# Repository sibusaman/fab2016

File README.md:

# Sibu's Fab Academy Documentation
Fab Academy 2016 Documentation License details

All of the documentations unless specified within the file or directory, is licensed under [CC-BY-SA 4.0](https://creativecommons.org/licenses/by-sa/4.0/legalcode) except for the source codes, which are licensed under [GPLv3](https://www.gnu.org/licenses/quick-guide-gplv3.en.html).

The following logo and it's varients are not shared under any licenses.

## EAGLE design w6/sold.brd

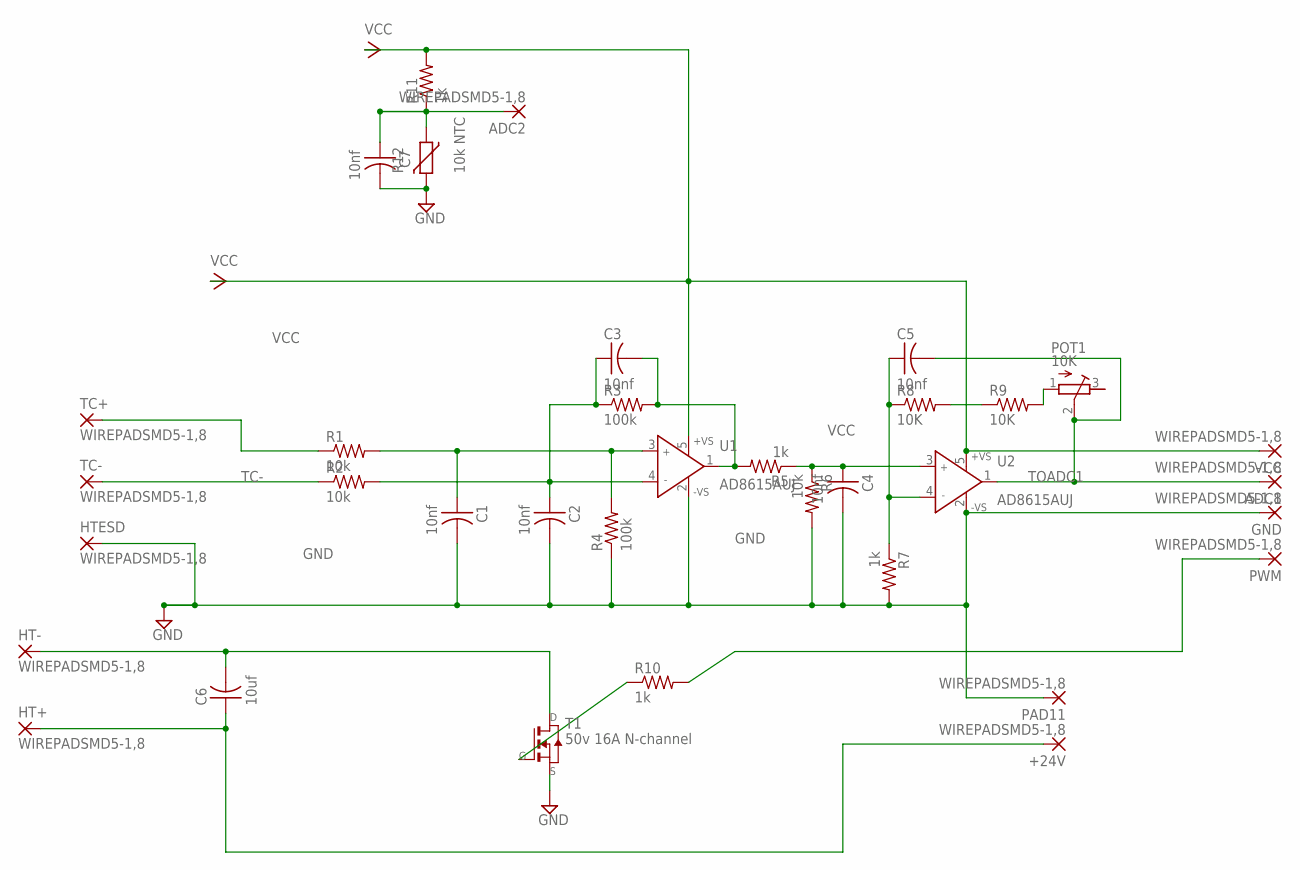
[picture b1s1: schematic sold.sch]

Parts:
+24V: WIREPADSMD5-1,8; 5-1,8
ADC1, ADC2: WIREPADSMD5-1,8; 5-1,8
C1, C2, C3, C4, C5, C7: 10nf; C1206FAB
C6: 10uf; C1206FAB
GND: WIREPADSMD5-1,8; 5-1,8
HT+: WIREPADSMD5-1,8; 5-1,8
HT-: WIREPADSMD5-1,8; 5-1,8
HTESD: WIREPADSMD5-1,8; 5-1,8
PAD11: WIREPADSMD5-1,8; 5-1,8
POT1: 10K; RTRIM3103
PWM: WIREPADSMD5-1,8; 5-1,8
R1, R2, R6: 10k; R1206FAB
R3, R4: 100k; R1206FAB
R5, R7, R10, R11: 1k; R1206FAB
R8, R9: 10K; R1206FAB
R12: 10k NTC; CT/CN1206
T1: 50v 16A N-channel; TO252
TC+: WIREPADSMD5-1,8; 5-1,8
TC-: WIREPADSMD5-1,8; 5-1,8
U1, U2: AD8615AUJ; TSOT23-5
VCC: WIREPADSMD5-1,8; 5-1,8

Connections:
GND: C1.2, C2.2, C4.2, C7.2, GND.1, HTESD.1, PAD11.1, R4.1, R6.2, R7.2, R12.2, T1.2 (S), U1.2 (-VS), U2.2 (-VS)
unnamed: C4.1, R5.1, R6.1, U2.3 (IN+)
unnamed: C2.1, C3.1, R2.2, R3.1, U1.4 (IN-)
unnamed: C3.2, R3.2, R5.2, U1.1 (OUT)
unnamed: R1.1, TC+.1
unnamed: ADC2.1, C7.1, R11.1, R12.1
unnamed: C1.1, R1.2, R4.2, U1.3 (IN+)
unnamed: R8.2, R9.1
unnamed: POT1.1 (A), R9.2
unnamed: C5.1, R7.1, R8.1, U2.4 (IN-)
unnamed: R10.1, T1.1 (G)
unnamed: PWM.1, R10.2
unnamed: +24V.1, C6.1, HT+.1
unnamed: C6.2, HT-.1, T1.3 (D)
TC-: R2.1, TC-.1
TOADC1: ADC1.1, C5.2, POT1.2 (S), U2.1 (OUT)
VCC: R11.2, U1.5 (+VS), U2.5 (+VS), VCC.1

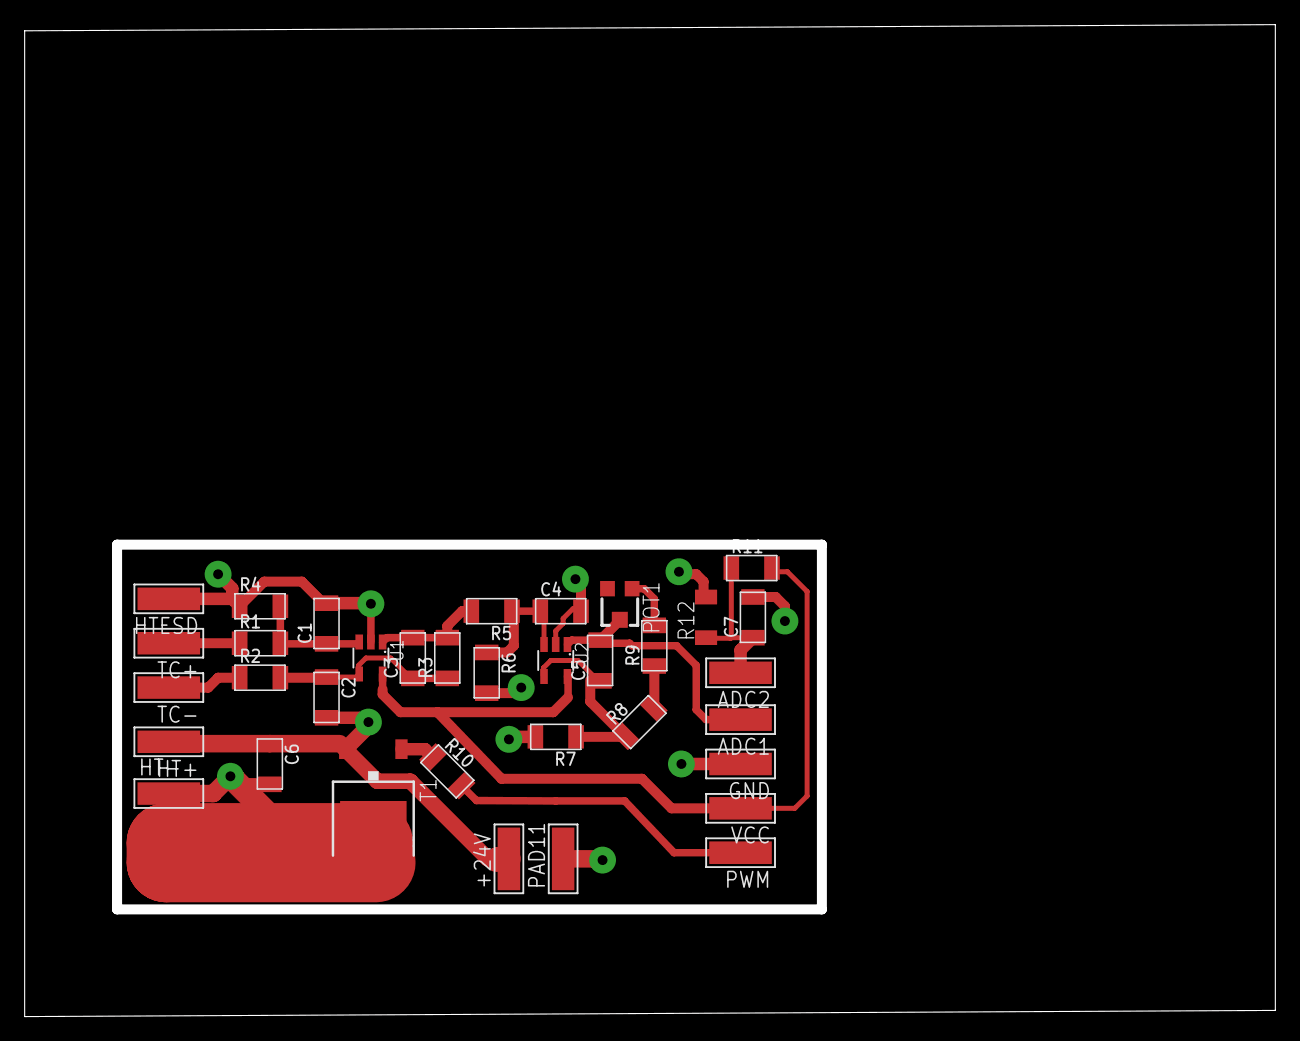
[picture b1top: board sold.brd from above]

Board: 2 copper layers, 101.5 x 80.5 mm, 35 parts (0 on the bottom side), 17 nets.

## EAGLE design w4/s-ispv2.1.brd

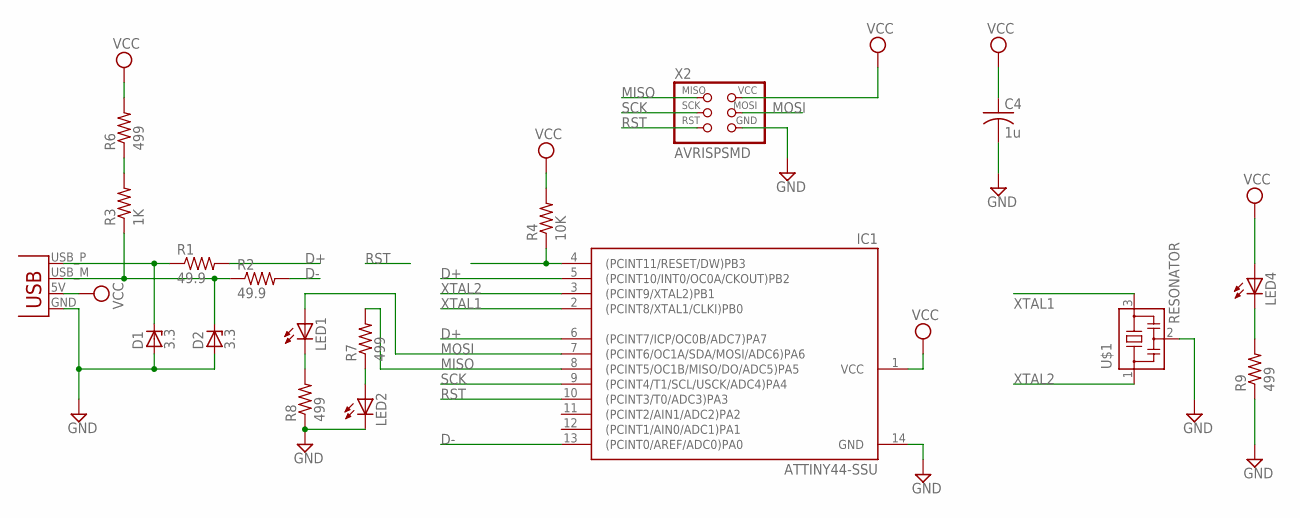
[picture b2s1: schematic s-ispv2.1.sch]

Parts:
C4: 1u; C1206
D1, D2: 3.3; SOD123
IC1: ATTINY44-SSU; SOIC14
LED1, LED2, LED4: LEDSMT1206; 1206
R1, R2: 49.9; R1206
R3: 1K; R1206
R4: 10K; R1206
R6, R7, R8, R9: 499; R1206
U$1: RESONATOR; EFOBM
X1: USBPCB; USB-A-PCB
X2: AVRISPSMD; 2X03SMD

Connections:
D+: IC1.5 ((PCINT10/INT0/OC0A/CKOUT)PB2), IC1.6 ((PCINT7/ICP/OC0B/ADC7)PA7), R1.2
D-: IC1.13 ((PCINT0/AREF/ADC0)PA0), R2.2
GND: C4.2, D1.ANODE, D2.ANODE, IC1.14 (GND), LED2.C, R8.1, R9.1, U$1.2, X1.GND, X2.6 (GND)
MISO: IC1.8 ((PCINT5/OC1B/MISO/DO/ADC5)PA5), R7.2, X2.1 (MISO)
MOSI: IC1.7 ((PCINT6/OC1A/SDA/MOSI/ADC6)PA6), LED1.A, X2.4 (MOSI)
unnamed: D1.CATHODE, R1.1, X1.USB_P (D+)
unnamed: D2.CATHODE, R2.1, R3.1, X1.USB_M (D-)
unnamed: R3.2, R6.1
unnamed: LED1.C, R8.2
unnamed: LED2.A, R7.1
unnamed: LED4.C, R9.2
RST: IC1.4 ((PCINT11/RESET/DW)PB3), IC1.10 ((PCINT3/T0/ADC3)PA3), R4.1, X2.5 (RST)
SCK: IC1.9 ((PCINT4/T1/SCL/USCK/ADC4)PA4), X2.3 (SCK)
VCC: C4.1, IC1.1 (VCC), LED4.A, R4.2, R6.2, X1.5V (VBUS), X2.2 (VCC)
XTAL1: IC1.2 ((PCINT8/XTAL1/CLKI)PB0), U$1.3
XTAL2: IC1.3 ((PCINT9/XTAL2)PB1), U$1.1

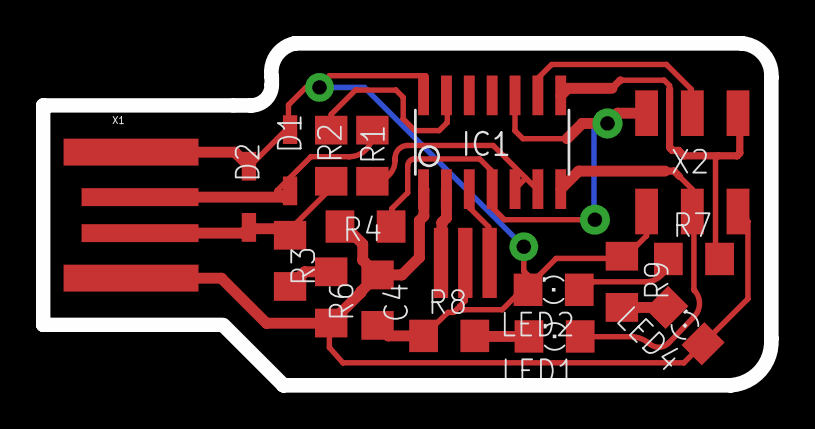
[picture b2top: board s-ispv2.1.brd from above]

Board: 2 copper layers, 40.4 x 19.0 mm, 18 parts (0 on the bottom side), 16 nets.

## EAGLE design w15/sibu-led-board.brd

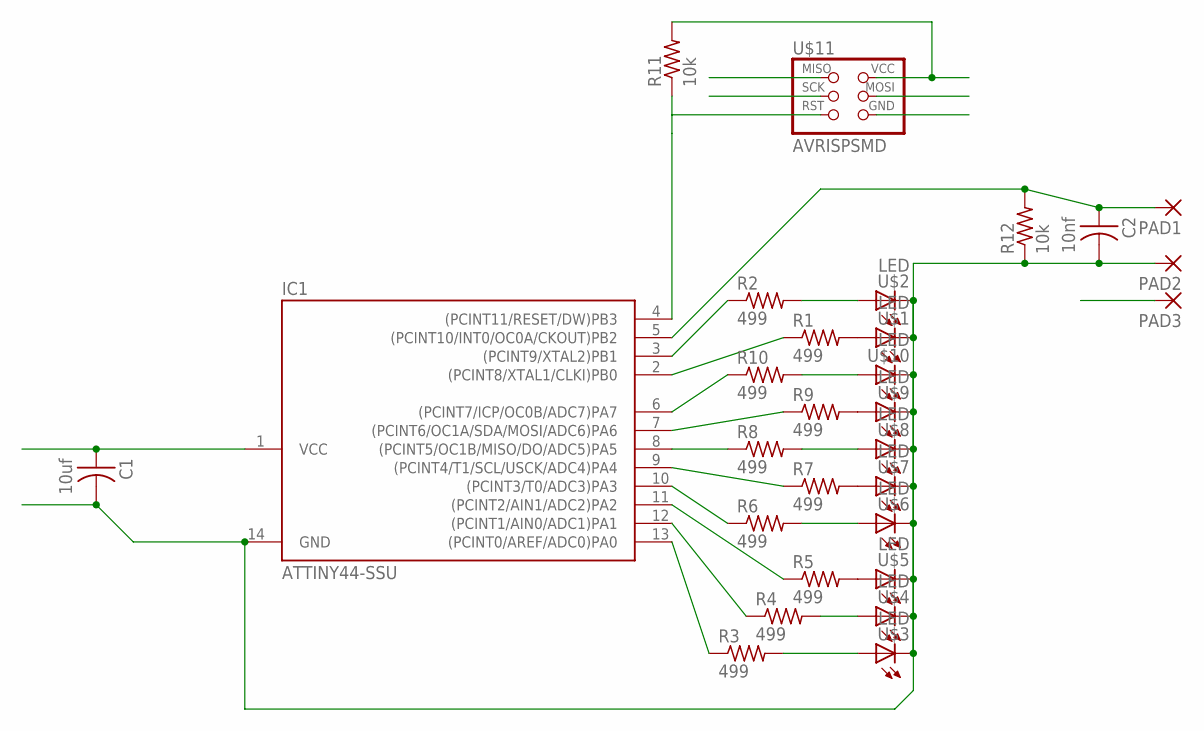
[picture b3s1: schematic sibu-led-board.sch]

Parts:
C1: 10uf; C1206FAB
C2: 10nf; C1206FAB
IC1: ATTINY44-SSU; SOIC14
PAD1, PAD2, PAD3: SMD2; SMD1,27-2,54
R1, R2, R3, R4, R5, R6, R7, R8, R9, R10: 499; R1206FAB
R11, R12: 10k; R1206FAB
U$1, U$2, U$3, U$4, U$5, U$6, U$7, U$8, U$9, U$10: LED; LED1206FAB
U$11: AVRISPSMD; 2X03SMD

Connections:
A0: R3.2, U$3.1 (A)
A1: R4.2, U$4.1 (A)
A2: R5.2, U$5.1 (A)
A3: R6.2, U$6.1 (A)
A4: R7.2, U$7.1 (A)
A5: R8.2, U$8.1 (A)
A6: R9.2, U$9.1 (A)
A7: R10.2, U$10.1 (A)
B0: R1.2, U$1.1 (A)
B1: R2.2, U$2.1 (A)
DATA_IN: C2.1, IC1.5 ((PCINT10/INT0/OC0A/CKOUT)PB2), PAD1.1, R12.2
GND: C1.2, C2.2, IC1.14 (GND), PAD2.1, R12.1, U$1.2 (C), U$2.2 (C), U$3.2 (C), U$4.2 (C), U$5.2 (C), U$6.2 (C), U$7.2 (C), U$8.2 (C), U$9.2 (C), U$10.2 (C), U$11.6 (GND)
MISO: IC1.8 ((PCINT5/OC1B/MISO/DO/ADC5)PA5), R8.1, U$11.1 (MISO)
MOSI: IC1.7 ((PCINT6/OC1A/SDA/MOSI/ADC6)PA6), R9.1, U$11.4 (MOSI)
unnamed: IC1.13 ((PCINT0/AREF/ADC0)PA0), R3.1
unnamed: IC1.12 ((PCINT1/AIN0/ADC1)PA1), R4.1
unnamed: IC1.11 ((PCINT2/AIN1/ADC2)PA2), R5.1
unnamed: IC1.10 ((PCINT3/T0/ADC3)PA3), R6.1
unnamed: IC1.2 ((PCINT8/XTAL1/CLKI)PB0), R1.1
unnamed: IC1.3 ((PCINT9/XTAL2)PB1), R2.1
unnamed: IC1.6 ((PCINT7/ICP/OC0B/ADC7)PA7), R10.1
RST: IC1.4 ((PCINT11/RESET/DW)PB3), R11.1, U$11.5 (RST)
SCK: IC1.9 ((PCINT4/T1/SCL/USCK/ADC4)PA4), R7.1, U$11.3 (SCK)
VCC: C1.1, IC1.1 (VCC), PAD3.1, R11.2, U$11.2 (VCC)

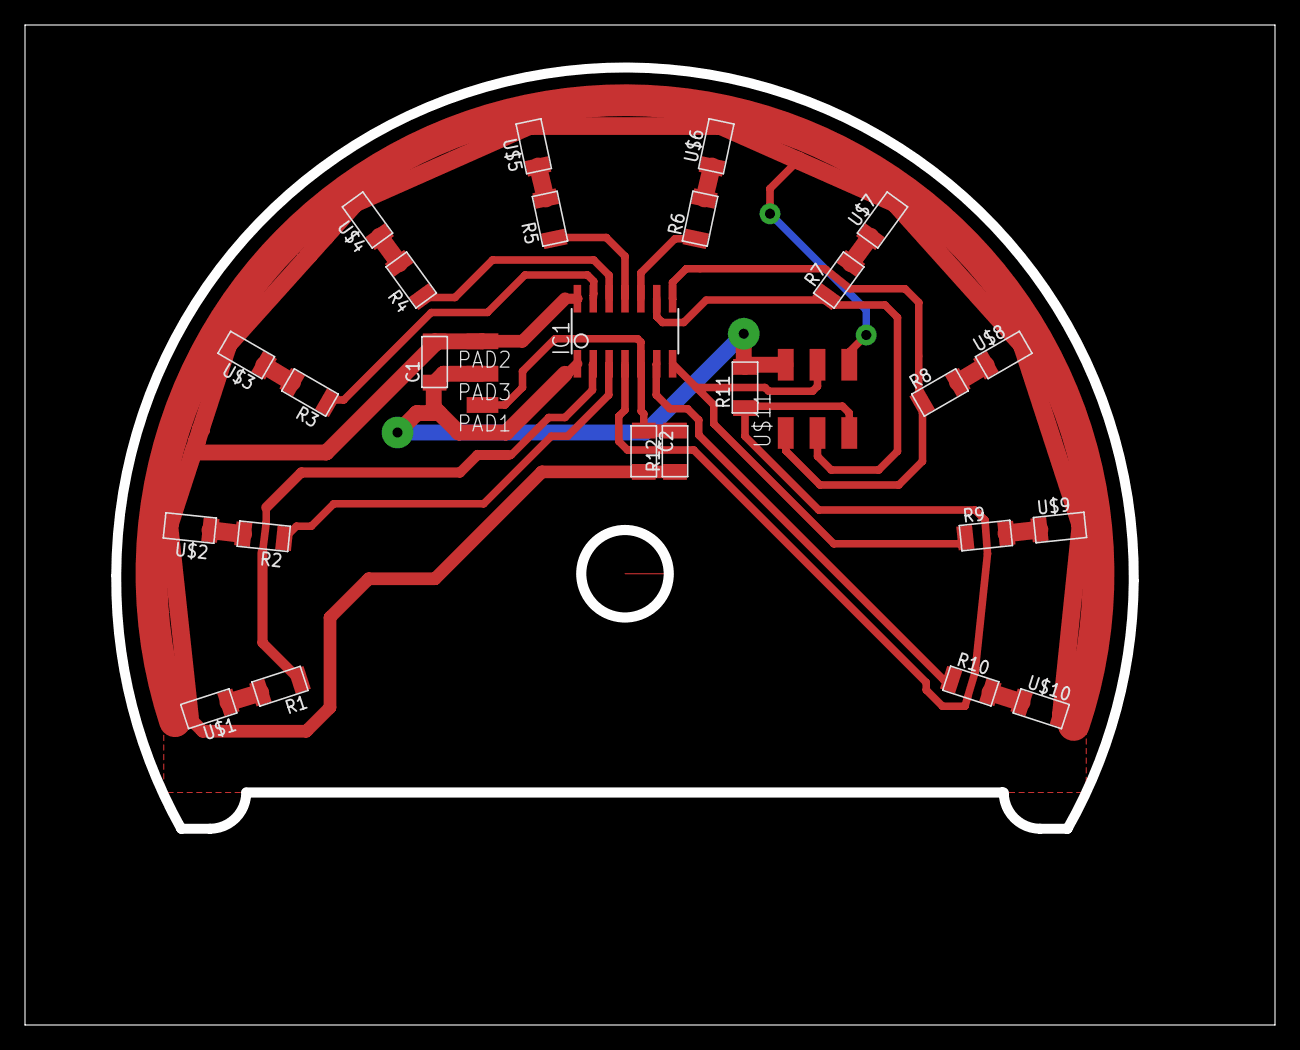
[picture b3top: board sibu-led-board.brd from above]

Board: 2 copper layers, 100.0 x 80.0 mm, 29 parts (0 on the bottom side), 24 nets.

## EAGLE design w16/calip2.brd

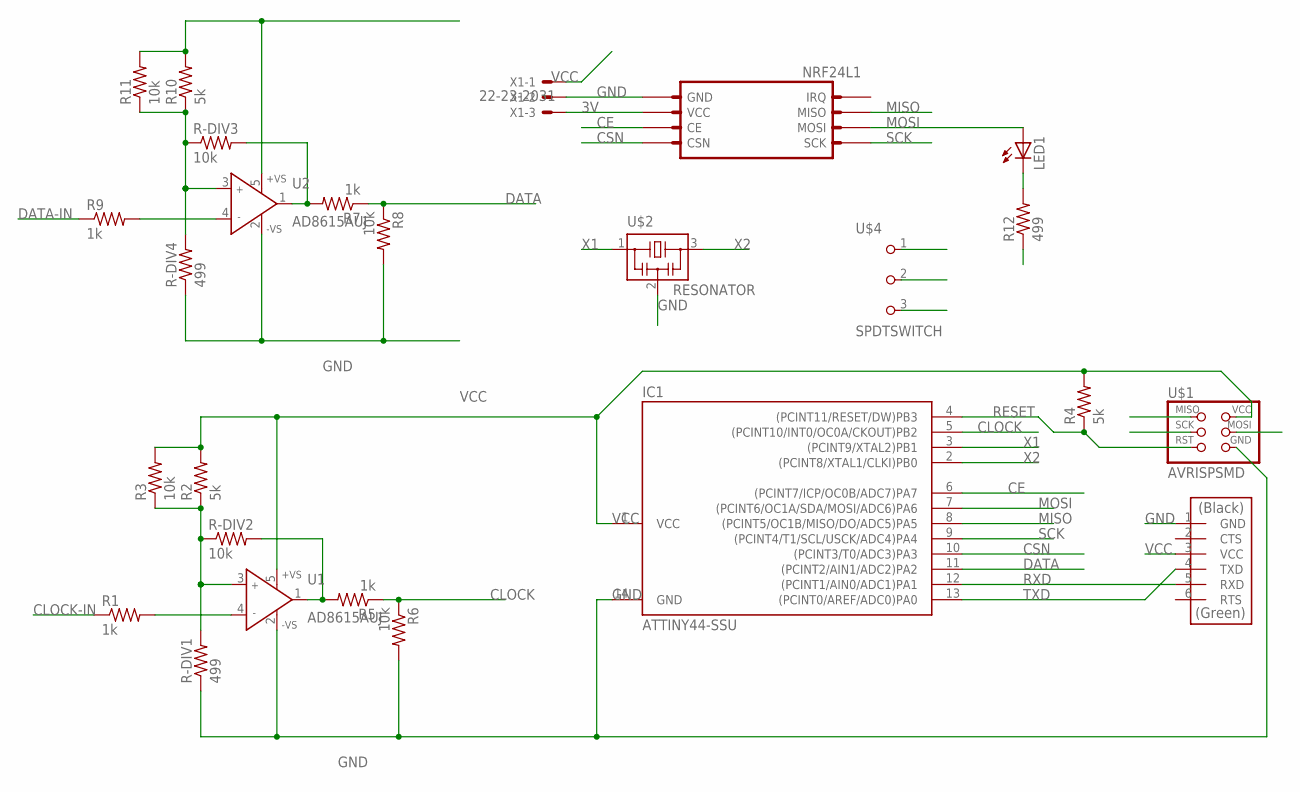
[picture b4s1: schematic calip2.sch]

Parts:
IC1: ATTINY44-SSU; SOIC14
LED1: LEDSML1206; SML1206
NRF24L1: NRF
R1, R5, R7, R9: 1k; R1206FAB
R2, R4, R10: 5k; R1206FAB
R3, R6, R8, R11: 10k; R1206FAB
R12: 499; R1206FAB
R-DIV1, R-DIV4: 499; R1206FAB
R-DIV2, R-DIV3: 10k; R1206FAB
U1, U2: AD8615AUJ; TSOT23-5
U$1: AVRISPSMD; 2X03SMD
U$2: RESONATOR; EFOBM
U$3: FTDI-SMD-HEADER; 1X06SMD
U$4: SPDTSWITCH
X1: 22-23-2031

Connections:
3V: NRF24L1.2 (VCC), X1.3
CE: IC1.6 ((PCINT7/ICP/OC0B/ADC7)PA7), NRF24L1.3 (CE)
CLOCK: IC1.5 ((PCINT10/INT0/OC0A/CKOUT)PB2), R5.1, R6.1
CLOCK-IN: R1.1, U$4.2
CSN: IC1.10 ((PCINT3/T0/ADC3)PA3), NRF24L1.4 (CSN)
DATA: IC1.11 ((PCINT2/AIN1/ADC2)PA2), R7.1, R8.1
DATA-IN: R9.1, U$4.3
GND: IC1.14 (GND), NRF24L1.P$1 (GND), R6.2, R8.2, R12.1, R-DIV1.1, R-DIV4.1, U1.2 (-VS), U2.2 (-VS), U$1.6 (GND), U$2.2, U$3.1 (GND), U$4.1, X1.2
MISO: IC1.8 ((PCINT5/OC1B/MISO/DO/ADC5)PA5), NRF24L1.7 (MISO), U$1.1 (MISO)
MOSI: IC1.7 ((PCINT6/OC1A/SDA/MOSI/ADC6)PA6), LED1.A, NRF24L1.6 (MOSI), U$1.4 (MOSI)
unnamed: R1.2, U1.4 (IN-)
unnamed: LED1.C, R12.2
unnamed: R2.1, R3.1, R-DIV1.2, R-DIV2.1, U1.3 (IN+)
unnamed: R5.2, R-DIV2.2, U1.1 (OUT)
unnamed: R7.2, R-DIV3.2, U2.1 (OUT)
unnamed: R10.1, R11.1, R-DIV3.1, R-DIV4.2, U2.3 (IN+)
unnamed: R9.2, U2.4 (IN-)
RESET: IC1.4 ((PCINT11/RESET/DW)PB3), R4.1, U$1.5 (RST)
RXD: IC1.12 ((PCINT1/AIN0/ADC1)PA1), U$3.5 (RXD)
SCK: IC1.9 ((PCINT4/T1/SCL/USCK/ADC4)PA4), NRF24L1.5 (SCK), U$1.3 (SCK)
TXD: IC1.13 ((PCINT0/AREF/ADC0)PA0), U$3.4 (TXD)
VCC: IC1.1 (VCC), R2.2, R3.2, R4.2, R10.2, R11.2, U1.5 (+VS), U2.5 (+VS), U$1.2 (VCC), U$3.3 (VCC), X1.1
X1: IC1.3 ((PCINT9/XTAL2)PB1), U$2.1
X2: IC1.2 ((PCINT8/XTAL1/CLKI)PB0), U$2.3

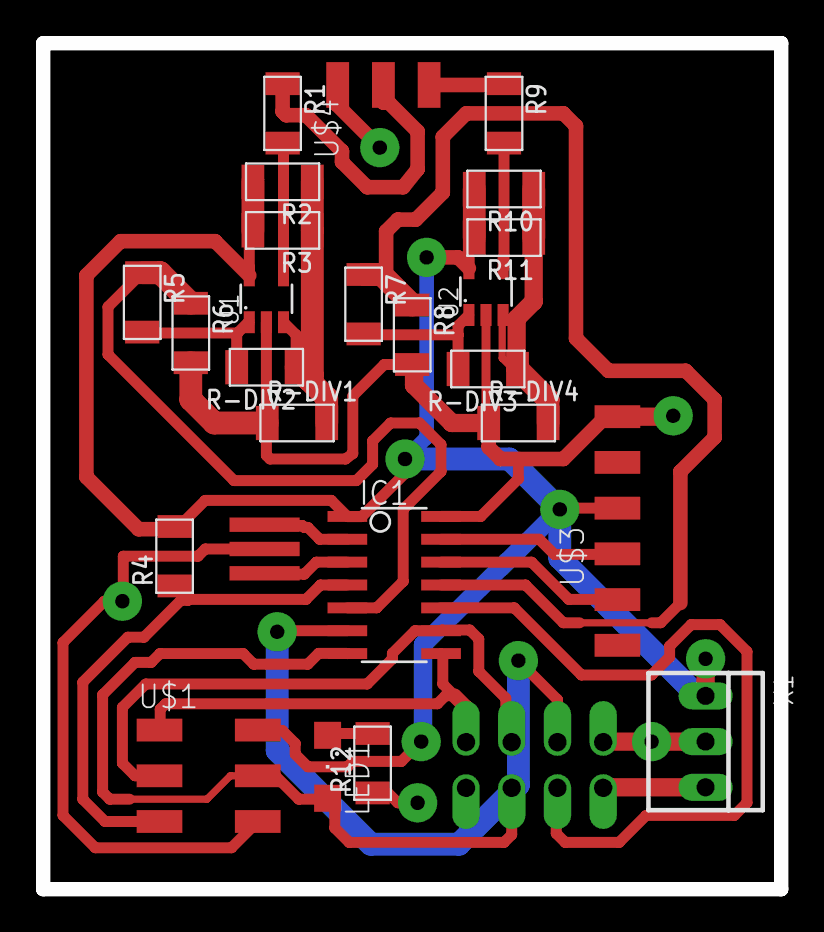
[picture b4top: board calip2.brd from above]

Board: 2 copper layers, 41.0 x 47.0 mm, 26 parts (1 on the bottom side), 24 nets.

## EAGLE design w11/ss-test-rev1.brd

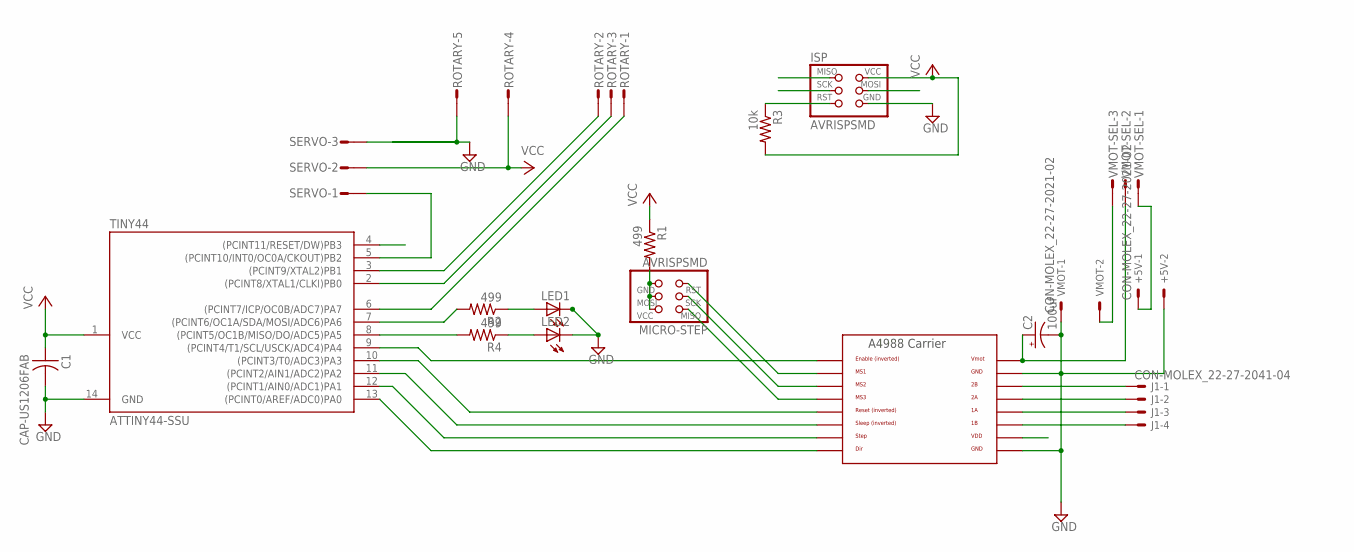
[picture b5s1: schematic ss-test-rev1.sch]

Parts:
+5V: CON-MOLEX_22-27-2021-02; CON-MOLEX_6410-02
A4988: REPRAPJR_A4988BREAKOUT
C1: CAP-US1206FAB; C1206FAB
C2: 100uf; RCL_140CLH-0810
ISP: AVRISPSMD; 2X03SMD
J1: CON-MOLEX_22-27-2041-04; CON-MOLEX_6410-04
LED1, LED2: LED_LEDSML1206; LED_SML1206
MICRO-STEP: AVRISPSMD; 2X03SMD
R1, R2, R4: 499; R1206FAB
R3: 10k; R1206FAB
ROTARY: S05P
SERVO: S03P
TINY44: ATTINY44-SSU; SOIC14
VMOT: CON-MOLEX_22-27-2021-02; CON-MOLEX_6410-02
VMOT-SEL: S03P

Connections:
GND: +5V.2, A4988.GND, A4988.GND@0 (GND), C1.2, C2.-, ISP.6 (GND), LED1.C, LED2.C, ROTARY.5, SERVO.3, TINY44.14 (GND), VMOT.1
MISO: ISP.1 (MISO), R4.2, TINY44.8 ((PCINT5/OC1B/MISO/DO/ADC5)PA5)
MOSI: ISP.4 (MOSI), R2.2, TINY44.7 ((PCINT6/OC1A/SDA/MOSI/ADC6)PA6)
unnamed: A4988.2B, J1.1
unnamed: A4988.2A, J1.2
unnamed: A4988.1A, J1.3
unnamed: A4988.1B, J1.4
unnamed: A4988.MS1, MICRO-STEP.5 (RST)
unnamed: A4988.MS2, MICRO-STEP.3 (SCK)
unnamed: A4988.MS3, MICRO-STEP.1 (MISO)
unnamed: ROTARY.2, TINY44.3 ((PCINT9/XTAL2)PB1)
unnamed: ROTARY.3, TINY44.2 ((PCINT8/XTAL1/CLKI)PB0)
unnamed: A4988.DIR, TINY44.13 ((PCINT0/AREF/ADC0)PA0)
unnamed: A4988.STEP, TINY44.12 ((PCINT1/AIN0/ADC1)PA1)
unnamed: A4988.SLP (SLEEP), TINY44.11 ((PCINT2/AIN1/ADC2)PA2)
unnamed: A4988.RST, TINY44.10 ((PCINT3/T0/ADC3)PA3)
unnamed: LED2.A, R4.1
unnamed: A4988.VMOT, C2.+, VMOT-SEL.2
unnamed: SERVO.1, TINY44.5 ((PCINT10/INT0/OC0A/CKOUT)PB2)
unnamed: MICRO-STEP.2 (VCC), MICRO-STEP.4 (MOSI), MICRO-STEP.6 (GND), R1.2
unnamed: VMOT.2, VMOT-SEL.3
unnamed: ROTARY.1, TINY44.6 ((PCINT7/ICP/OC0B/ADC7)PA7)
unnamed: LED1.A, R2.1
RST: ISP.5 (RST), R3.1, TINY44.4 ((PCINT11/RESET/DW)PB3)
SCK: A4988.EN, ISP.3 (SCK), TINY44.9 ((PCINT4/T1/SCL/USCK/ADC4)PA4)
VCC: +5V.1, A4988.VDD, C1.1, ISP.2 (VCC), R1.1, R3.2, ROTARY.4, SERVO.2, TINY44.1 (VCC), VMOT-SEL.1

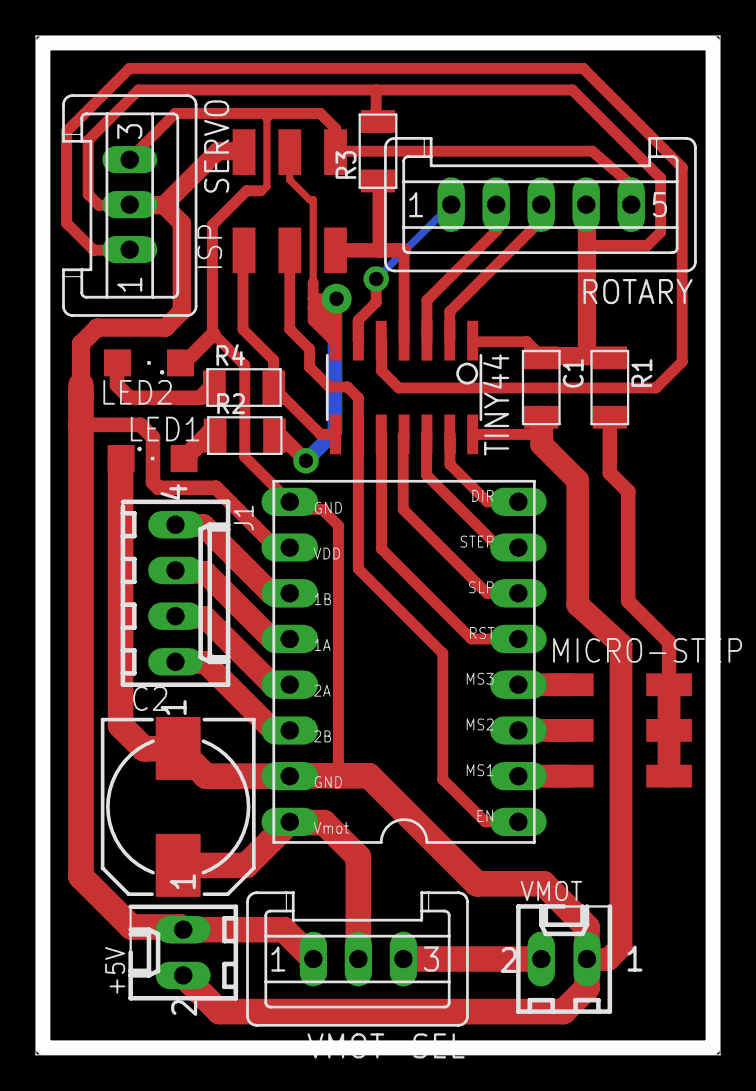
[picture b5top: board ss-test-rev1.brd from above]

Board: 2 copper layers, 38.0 x 56.6 mm, 18 parts (0 on the bottom side), 26 nets.

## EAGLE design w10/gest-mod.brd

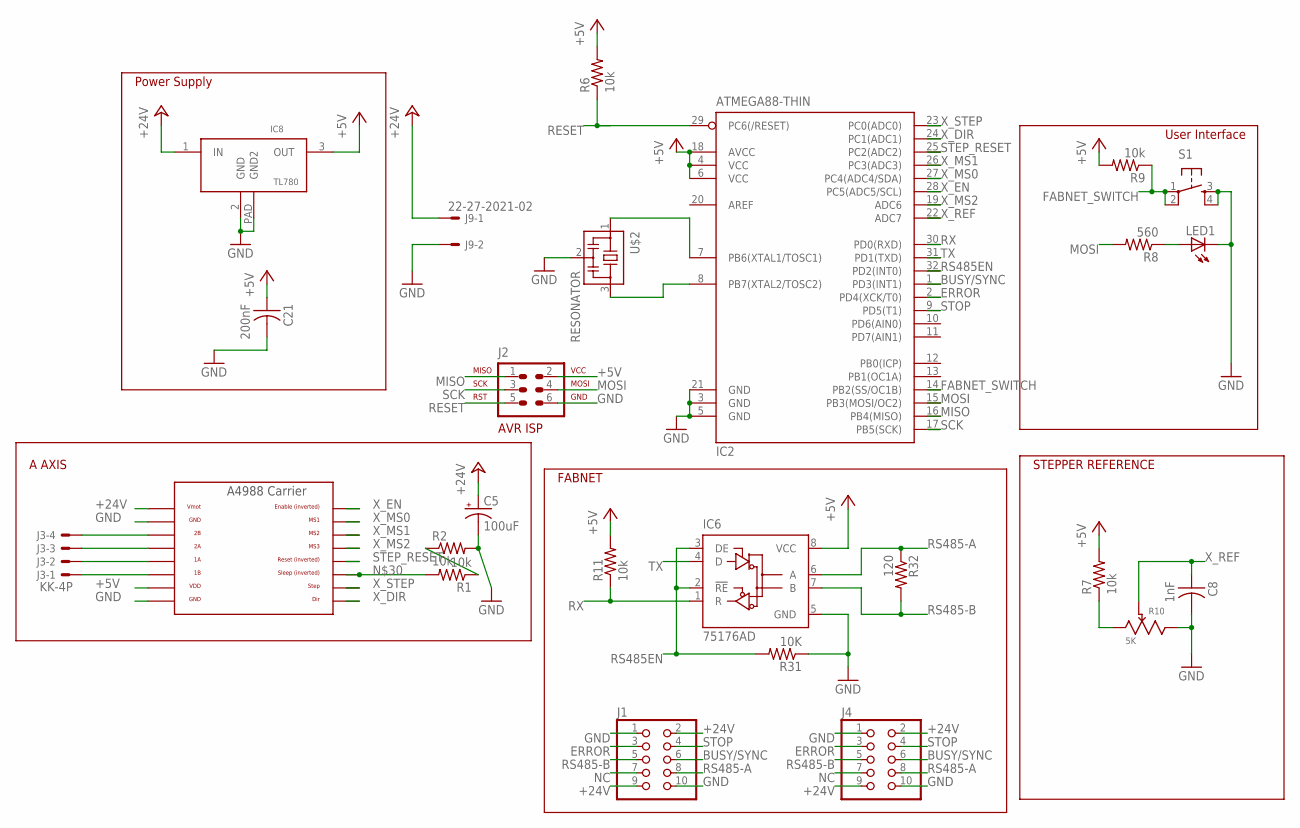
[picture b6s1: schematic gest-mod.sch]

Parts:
C5: 100uF; PANASONIC_D
C8: 1nF; C1206FAB
C21: 200nF; C1206FAB
IC2: ATMEGA88-THIN; TQFP32-08THIN
IC6: 75176AD; D_R-PDSO-G8
IC8: TL780_VREG; D2PAK-3
J1, J4: PINHEAD_PINHD-2X5; PINHEAD_2X05
J2: AVR-7_AVR-ISP-6VERT; AVR-7_AVR-ISP-6
J3: KK-4P; 7395-04
J9: 22-27-2021-02; 6410-02
LED1: LEDCHIPLED_1206; CHIPLED_1206
R1, R2, R6, R7, R9, R11: 10k; R1206FAB
R8: 560; R1206FAB
R10: 5K; BOURN_TRIM
R31: 10K; R1206FAB
R32: 120; R1206FAB
S1: 6MM_SWITCH6MM_SWITCH; 6MM_SWITCH
U$2: RESONATOR; EFOBM
U$5: REPRAPJR_A4988BREAKOUT

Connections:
+5V: C21.1, IC2.4 (VCC), IC2.6 (VCC), IC2.18 (AVCC), IC6.8 (VCC), IC8.3 (OUT), J2.2, R6.2, R7.2, R9.2, R11.2, U$5.VDD
+24V: C5.+, IC8.1 (IN), J1.2, J1.9, J4.2, J4.9, J9.1, U$5.VMOT
BUSY/SYNC: IC2.1 (PD3(INT1)), J1.6, J4.6
ERROR: IC2.2 (PD4(XCK/T0)), J1.3, J4.3
FABNET_SWITCH: IC2.14 (PB2(SS/OC1B)), R9.1, S1.1, S1.2 (P1)
GND: C5.-, C8.2, C21.2, IC2.3 (GND), IC2.5 (GND), IC2.21 (GND), IC6.5 (GND), IC8.2 (GND), IC8.PAD (GND2), J1.1, J1.10, J2.6, J4.1, J4.10, J9.2, LED1.C, R2.2, R10.3, R31.1, S1.3 (S), S1.4 (S1), U$2.2, U$5.GND, U$5.GND@0 (GND)
MISO: IC2.16 (PB4(MISO)), J2.1
MOSI: IC2.15 (PB3(MOSI/OC2)), J2.4, R8.2
N2354: R7.1, R10.1
unnamed: IC2.7 (PB6(XTAL1/TOSC1)), U$2.1
unnamed: IC2.8 (PB7(XTAL2/TOSC2)), U$2.3
unnamed: J3.3, U$5.2A
unnamed: J3.4, U$5.2B
unnamed: LED1.A, R8.1
unnamed: R1.1, R2.1
unnamed: J3.2, U$5.1A
unnamed: J3.1, U$5.1B
unnamed: R1.2, U$5.SLP (SLEEP)
NC: J1.7, J4.7
RESET: IC2.29 (PC6(/RESET)), J2.5, R6.1
RS485-A: IC6.6 (A), J1.8, J4.8, R32.1
RS485-B: IC6.7 (B), J1.5, J4.5, R32.2
RS485EN: IC2.32 (PD2(INT0)), IC6.2 (!RE), IC6.3 (DE), R31.2
RX: IC2.30 (PD0(RXD)), IC6.1 (R), R11.1
SCK: IC2.17 (PB5(SCK)), J2.3
STEP_RESET: IC2.25 (PC2(ADC2)), U$5.RST
STOP: IC2.9 (PD5(T1)), J1.4, J4.4
TX: IC2.31 (PD1(TXD)), IC6.4 (D)
X_DIR: IC2.24 (PC1(ADC1)), U$5.DIR
X_EN: IC2.28 (PC5(ADC5/SCL)), U$5.EN
X_MS0: IC2.27 (PC4(ADC4/SDA)), U$5.MS1
X_MS1: IC2.26 (PC3(ADC3)), U$5.MS2
X_MS2: IC2.19 (ADC6), U$5.MS3
X_REF: C8.1, IC2.22 (ADC7), R10.2
X_STEP: IC2.23 (PC0(ADC0)), U$5.STEP

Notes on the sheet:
A AXIS
Power Supply
FABNET
STEPPER REFERENCE
User Interface

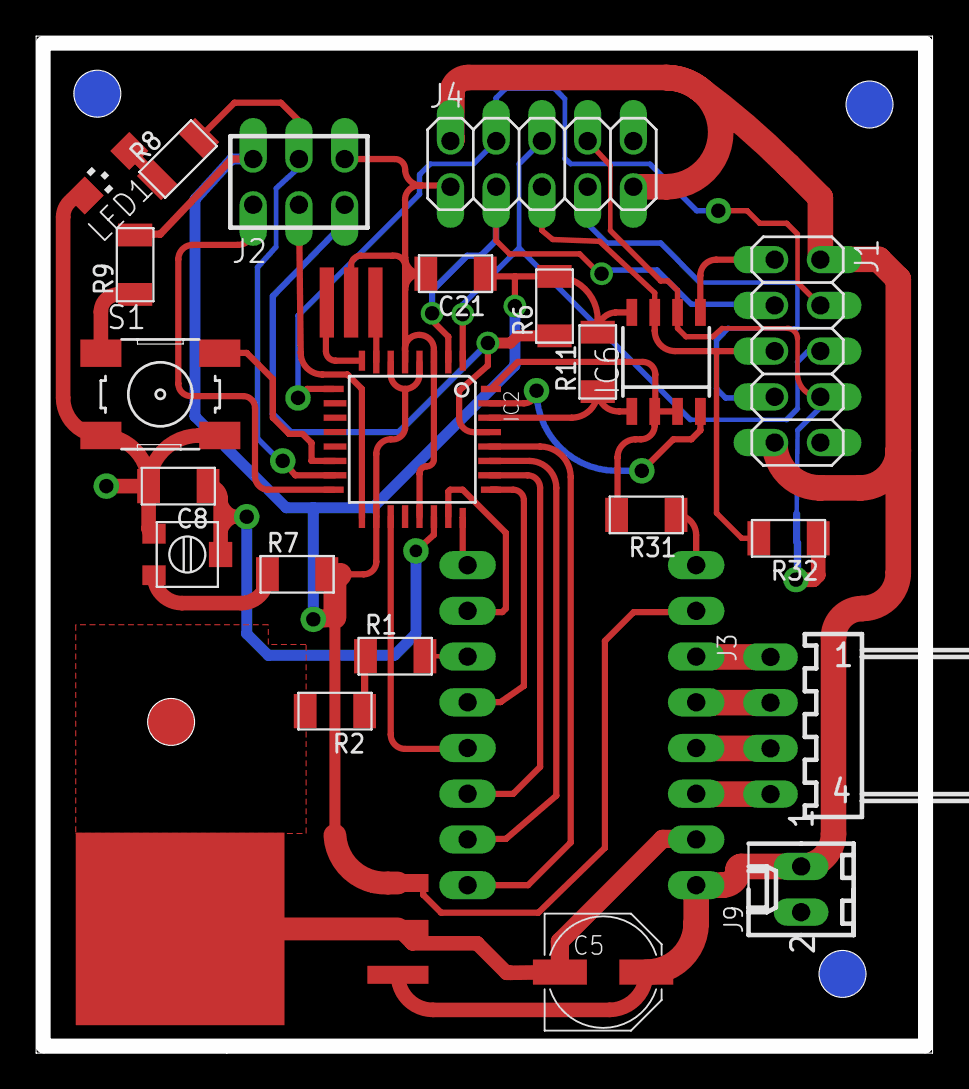
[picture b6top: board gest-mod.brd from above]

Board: 2 copper layers, 49.8 x 56.5 mm, 25 parts (1 on the bottom side), 35 nets.

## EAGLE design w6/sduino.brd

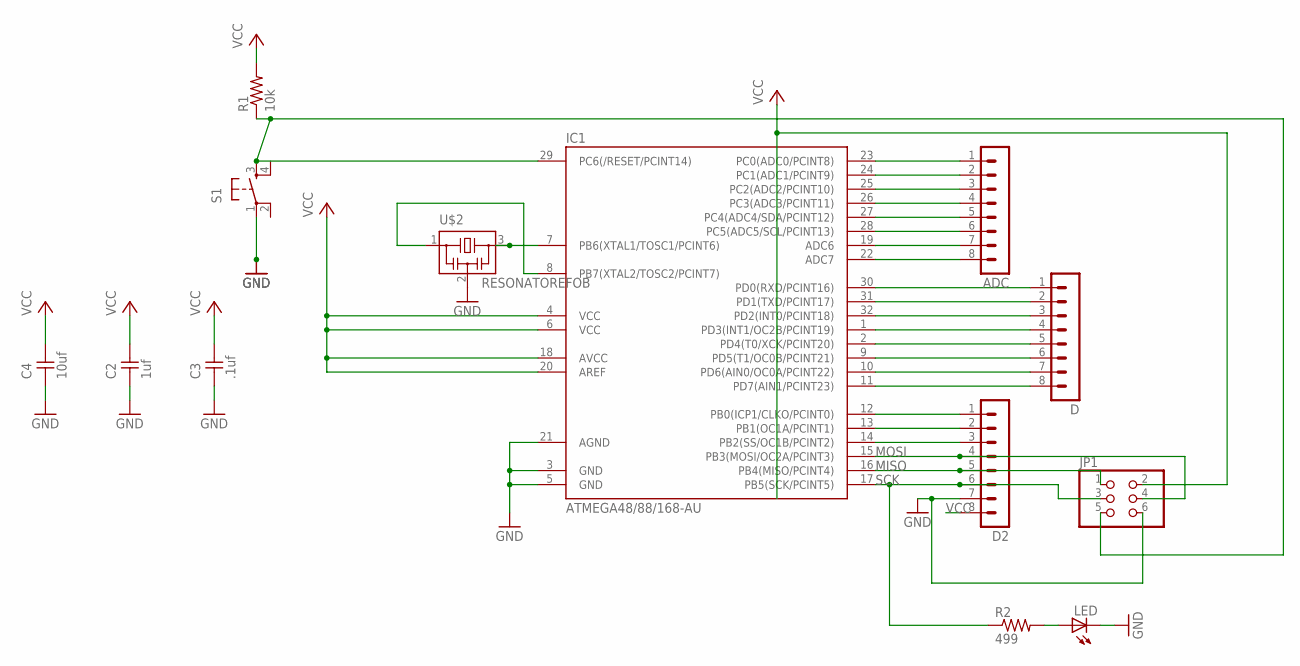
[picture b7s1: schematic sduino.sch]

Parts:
ADC: MA08-1
C2: 1uf; 1206
C3: .1uf; 1206
C4: 10uf; 1206
D, D2: MA08-1
IC1: ATMEGA48/88/168-AU; TQFP32-08
JP1: PINHD-2X3; 2X03
LED: LED1206; 1206
R1: 10k; 1206
R2: 499; 1206
S1: 6MM_SWITCH6MM_SWITCH; 6MM_SWITCH
U$2: RESONATOREFOB; EFOBM

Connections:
GND: C2.1, C3.1, C4.1, D2.7, IC1.3 (GND), IC1.5 (GND), IC1.21 (AGND), JP1.6, LED.2 (C), S1.1, U$2.2
MISO: D2.5, IC1.16 (PB4(MISO/PCINT4)), JP1.1
MOSI: D2.4, IC1.15 (PB3(MOSI/OC2A/PCINT3)), JP1.4
unnamed: IC1.8 (PB7(XTAL2/TOSC2/PCINT7)), U$2.1
unnamed: D2.1, IC1.12 (PB0(ICP1/CLKO/PCINT0))
unnamed: ADC.1, IC1.23 (PC0(ADC0/PCINT8))
unnamed: ADC.2, IC1.24 (PC1(ADC1/PCINT9))
unnamed: ADC.3, IC1.25 (PC2(ADC2/PCINT10))
unnamed: ADC.4, IC1.26 (PC3(ADC3/PCINT11))
unnamed: ADC.5, IC1.27 (PC4(ADC4/SDA/PCINT12))
unnamed: ADC.6, IC1.28 (PC5(ADC5/SCL/PCINT13))
unnamed: IC1.7 (PB6(XTAL1/TOSC1/PCINT6)), U$2.3
unnamed: D.3, IC1.32 (PD2(INT0/PCINT18))
unnamed: D.4, IC1.1 (PD3(INT1/OC2B/PCINT19))
unnamed: D.5, IC1.2 (PD4(T0/XCK/PCINT20))
unnamed: D.6, IC1.9 (PD5(T1/OC0B/PCINT21))
unnamed: D.7, IC1.10 (PD6(AIN0/OC0A/PCINT22))
unnamed: D.8, IC1.11 (PD7(AIN1/PCINT23))
unnamed: D2.2, IC1.13 (PB1(OC1A/PCINT1))
unnamed: D2.3, IC1.14 (PB2(SS/OC1B/PCINT2))
unnamed: ADC.7, IC1.19 (ADC6)
unnamed: ADC.8, IC1.22 (ADC7)
unnamed: LED.1 (A), R2.2
RST: IC1.29 (PC6(/RESET/PCINT14)), JP1.5, R1.1, S1.3 (S)
RX: D.1, IC1.30 (PD0(RXD/PCINT16))
SCK: D2.6, IC1.17 (PB5(SCK/PCINT5)), JP1.3, R2.1
TX: D.2, IC1.31 (PD1(TXD/PCINT17))
VCC: C2.2, C3.2, C4.2, D2.8, IC1.4 (VCC), IC1.6 (VCC), IC1.18 (AVCC), IC1.20 (AREF), JP1.2, R1.2

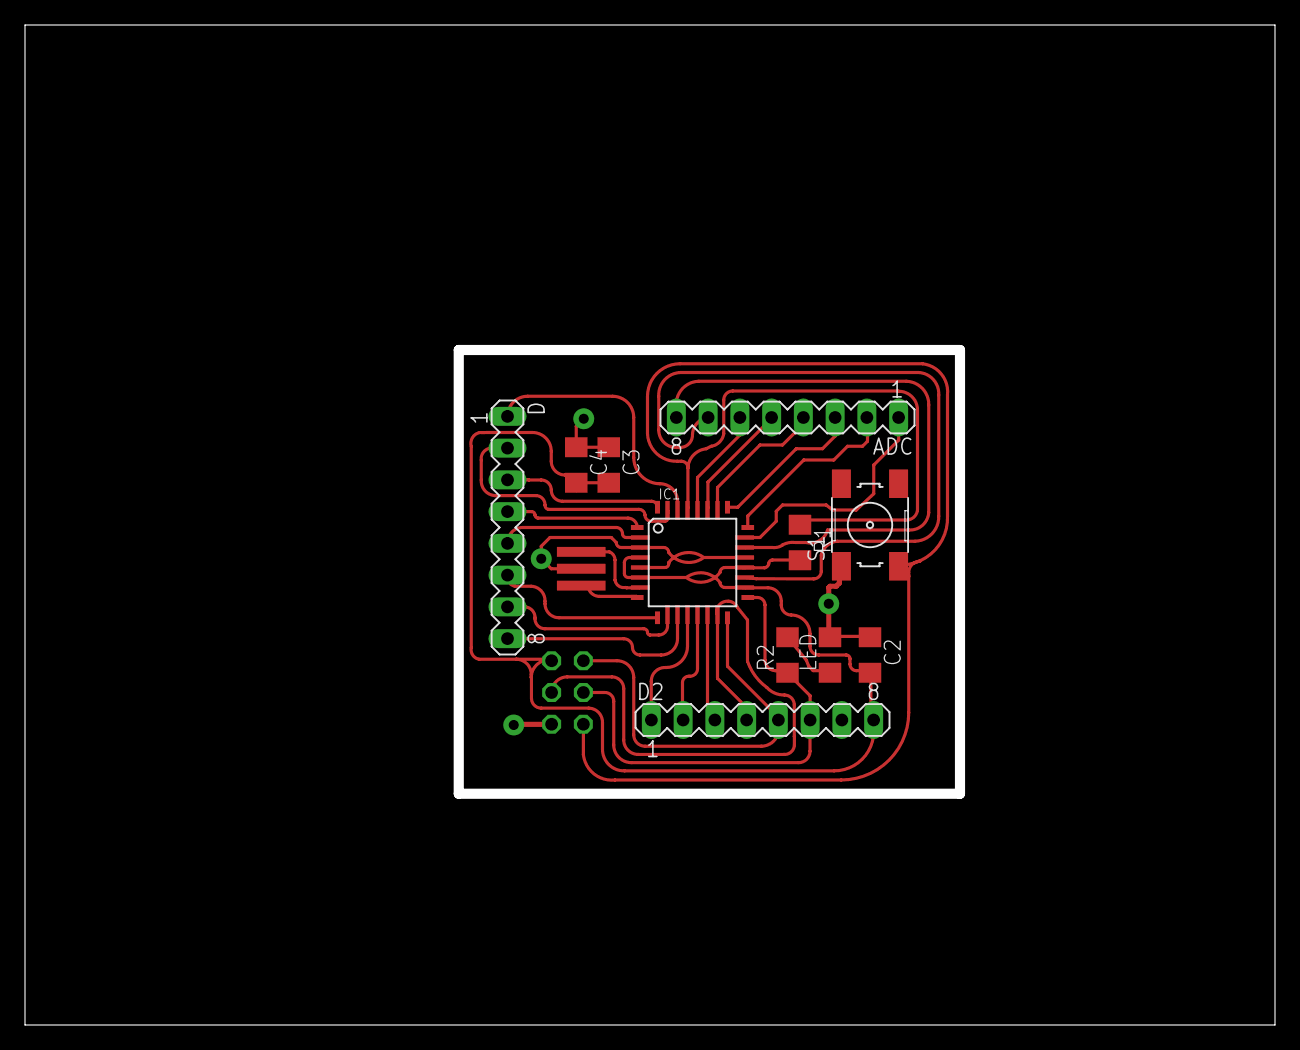
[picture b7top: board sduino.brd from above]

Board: 2 copper layers, 100.0 x 80.0 mm, 13 parts (1 on the bottom side), 28 nets.

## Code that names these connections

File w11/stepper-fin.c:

/*
shared under GPLv3
Author SIBU SAMAN
code for controlling the speed and the direction of a stepepr motor using a
rotary encoder
*/
#define F_CPU 8000000UL
#include <avr/interrupt.h>
#include <avr/io.h>
/*
  PA0		dir
  PA1		step
  PA2		sleep
  PA3		reset
  PA4		enable
  PA5		orange LED
  PA6		Blue LED

  Rotate the knob to adjust the speed of rotation and use the built-in
  push-button to toggle the direction.
 */

int temp = 20000;
int step = 1000;

void update(void);

int main(void) {
  DDRA |= (1 << PA6) | (1 << PA5) | (1 << PA4) | (1 << PA3) | (1 << PA2) |
          (1 << PA1) | (1 << PA0);
  PORTA |= (0 << PA5); // orange led
  // initialize Timer1 the 16bit timer
  cli(); // disable global interrupts
  TCCR1A = 0;
  TCCR1B = 0;

  // set compare match register to desired timer count:
  OCR1A = temp;

  TCCR1B |= (1 << WGM12); // turn on CTC mode:
  TCCR1B |= (1 << CS11);  // Use CS10, CS11 and CS12 bits for 1/8 prescaler:

  // enable timer compare interrupt:
  TIMSK1 |= (1 << OCIE1A);

  // enble pin change interrupts on porta and portb
  GIMSK |= (1 << PCIE0) | (1 << PCIE1); // PCICR is GIMSK in attiny

  // enable external interrupts for rotary switch
  PCMSK0 |= (1 << PCINT7); // CLK of Rotary
  PCMSK1 |= (1 << PCINT8); // push button of Rotary

  sei(); // enable global interrupts:

  PORTA |= (1 << PA3) | (1 << PA2); // sleep and reset
  PORTA |= (0 << PA4);              // enable
  while (1) {
    OCR1A = temp;
  }
}

ISR(TIM1_COMPA_vect) {
  PORTA ^= (1 << PA1);
  PORTA ^= (1 << PA5);
}
ISR(PCINT1_vect) {
  if ((PINB & 0b00000001)) {
    PORTA ^= (1 << PA6);
    PORTA ^= (1 << PA0); // change direction on push button
  }
}

ISR(PCINT0_vect) {
  if ((PINB & 0b00000001))
    update();
}
void update(void) {
  if (PINA & 0b10000000)
    if (PINB & 0b00000010)
      temp -= step;
    else
      temp += step;
  step = temp / 30;
  if (temp > 25000)
    temp = 25000;
  if (temp < 600)
    temp = 600;
  if (step < 10)
    step = 10;
}

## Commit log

2016-02-01 Create gh-pages branch via GitHub
2016-02-01 first update to the site
2016-02-02 redirected
2016-02-02 draft update
2016-02-02 week1 fix theme
2016-02-02 week1 'drawbacks tab;e'
2016-02-02 week1 edit heading
2016-02-02 week1 edit heading typo
2016-02-02 index page edit
2016-02-02 new content
2016-02-02 change w1 draft pic
2016-02-08 w1 add
2016-02-08 w2 begin
2016-02-08 hardware setup
2016-02-08 trial one images and vid
2016-02-08 heading style
2016-02-08 ssd links
2016-02-10 w1-update
2016-02-11 w2-3d
2016-02-12 w3-content
2016-02-12 w3-content-typo
2016-02-12 w3 anim
2016-02-15 heavy mod
2016-02-17 2d-firstcommit
2016-02-17 w3-laser-firstcommit
2016-02-17 w3-typo
2016-02-17 edit image
2016-02-17 vinyl-first-commit
2016-02-19 edit+w4
2016-02-25 w4+w5-init
2016-03-01 w5-content
2016-03-02 w5-pic-gallery
2016-03-02 w5-assem
2016-03-03 w4-ispv2
2016-03-03 w5-troubleshoot
2016-03-03 w5-print and w6 page
2016-03-03 resize few images
2016-03-05 s-isp-v2
2016-03-05 Klien-flask
2016-03-05 soldering station contents
2016-03-05 typo
2016-03-05 resize images
2016-03-06 box openscad update
2016-03-06 w5 more content
2016-03-07 dock final pic
2016-03-08 w6-list
2016-03-08 massive syntax correction
2016-03-09 sduino-brd
2016-03-10 w7-first commit, s-ispv2 final pics
2016-03-10 s-ispv2 debug
2016-03-10 sisp final pics and evo
2016-03-10 bg print fail video
2016-03-11 isp finish
2016-03-11 w6 more
2016-03-13 w7 idea
2016-03-15 w7 resize
2016-03-15 w7 update
2016-03-17 arduino in arch
2016-03-17 arduino fix add
2016-03-17 arduino fix typo
2016-03-17 w8, new window header
2016-03-17 w8, set goals
2016-03-18 w8 sduino resonator fix
2016-03-22 w10 gest write
2016-03-31 sibu w9, w10, gestalt node update
2016-03-31 gestalt node update
2016-04-01 w8 timer code
2016-04-02 w8 timer code asm
2016-04-02 w8 resour
2016-04-04 w9 begin
2016-04-06 sibu:- update gest
2016-04-07 sibu:- update w9, scrapyard
2016-04-12 windup, going home
2016-04-13 machine week
2016-04-13 machine design
2016-04-19 input devices
2016-04-22 step-ser control rev-1
2016-04-24 step-ser pgms
2016-04-29 w11 bounce
2016-05-03 w11 stepper code
2016-05-03 w11 reset pullup
2016-05-09 w11 servo-esc fin
2016-05-09 w12 mold
2016-05-12 m8-babbitt pics
2016-05-18 m8-babbitt doc
2016-05-19 w15 w16 and w8 micro datasheet
2016-05-28 calip first commit
2016-05-29 calip prgm
2016-05-29 all weeks page
2016-05-29 all weeks page, calip, image click to zoom
2016-05-31 project first commit
2016-05-31 project
2016-05-31 project-doc
2016-06-01 casting video
2016-06-01 w17 almost over
2016-06-01 vishnu
2016-06-01 testimonial
2016-06-09 wire-feeder-test
2016-06-09 box mutant
2016-06-16 box mutant lathe
2016-06-27 networking
2016-06-27 networking-done
2016-06-28 networking-identity draft and time lapse
2016-06-29 index.html w6 link fix
2016-06-29 w12 modela machining
2016-06-30 image zoom property change, w12 more images, ISP updated with LED
2016-06-30 w4 fix link
2016-06-30 image hover zoom icon cursor
2016-06-30 w4 w3 done, photos videos time lapse coil test....
2016-07-01 s-isp firmware
2016-07-02 modela scan. project corrections fath
2016-07-03 composite till demold
2016-07-03 3d print wrapup
2016-07-04 composite done, w3 typo
2016-07-04 w17 windup
2016-07-04 IP CC done GPL coming
2016-07-04 IP done
2016-07-04 create CC-BY-SA lisence
2016-07-04 Rename license.md to README.md
2016-07-04 license files added
2016-07-04 IP update
2016-07-05 w4 w5 w18 proof-read w7 update w14 image fix
2016-07-05 w7 till final cut pattern
2016-07-06 shopbot done and many other typos and w6 8 9 10 11 12 proof
2016-07-06 14 15 proof
2016-07-06 15 16 proof
2016-07-07 16-17-18 proof, interface done
2016-07-07 site header redone
2016-07-07 project progress
2016-07-08 project progress rhino file
2016-07-12 project progress schematics
2016-07-12 project progress schematics done
2016-07-12 project progress schematics original done
2016-07-13 networking wind-up
2016-07-13 project pics of crap boards
2016-07-25 fixes
2016-07-25 fixes except final project
2016-07-26 fixes for final project
2016-07-28 final fixes for final project
